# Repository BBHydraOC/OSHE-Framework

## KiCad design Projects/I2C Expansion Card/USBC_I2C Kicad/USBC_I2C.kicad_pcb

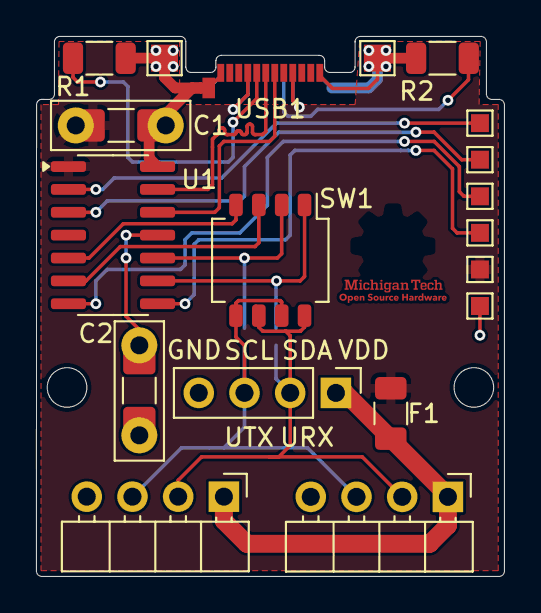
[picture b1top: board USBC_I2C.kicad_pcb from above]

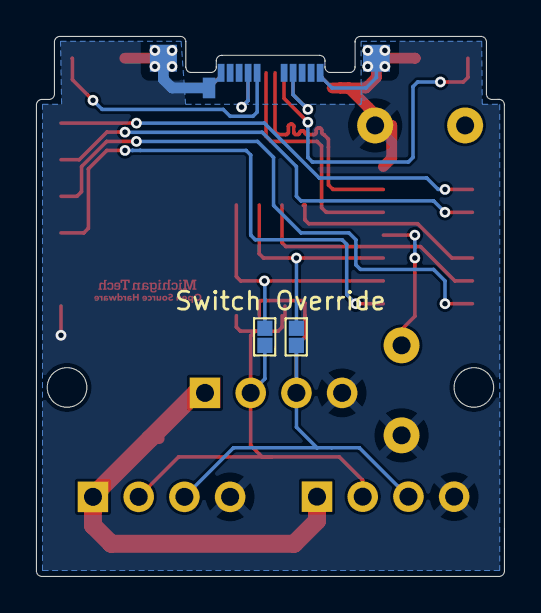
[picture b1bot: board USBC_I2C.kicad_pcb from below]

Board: 2 copper layers, 26.0 x 30.0 mm, 14 parts (2 on the bottom side), 13 nets.

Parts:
2x Pads, 2x Pads#2: Jumper Pads
C1: 0.47uF; C_1206_3216Metric_Pad1.33x1.80mm_HandSolder
C2: 0.22uF; C_1206_3216Metric_Pad1.33x1.80mm_HandSolder
F1: Polyfuse; Fuse_1206_3216Metric
H1, H2: MountingHole; MountingHole_2.2mm_M2
R1: 5.1k; R_1206_3216Metric
R2: Resistors TBD; R_1206_3216Metric
SW1: SW_DIP_x04; SW_DIP_SPSTx04_Slide_Omron_A6H-4101_W6.15mm_P1.27mm
TP3, TP3#2: TestPoint; TestPoint_Pad_1.5x1.5mm
U1: MCP2221AxSL; SOIC-14_3.9x8.7mm_P1.27mm
USB1: USB C Male Connector; USB_C_Plug_Molex_105444

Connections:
GND: C1.1, C2.1, R1.2, R2.2, TP3.1, TP3#2.1, U1.14 (VSS), USB1.A1 (GND), USB1.A12 (GND), USB1.B1 (GND), USB1.B12 (GND), USB1.S1 (SHIELD)
unnamed: U1.13 (D+), USB1.A6 (D+)
unnamed: U1.12 (D-), USB1.A7 (D-)
unnamed: 2x Pads#2.1, SW1.2, U1.10 (SCL)
unnamed: 2x Pads.1, SW1.1, U1.9 (SDA)
unnamed: SW1.4, U1.5 (URx)
unnamed: SW1.3, U1.6 (UTx)
unnamed: C1.2, F1.1, U1.1 (VDD), USB1.A4 (VBUS), USB1.A9 (VBUS), USB1.B4 (VBUS), USB1.B9 (VBUS)
unnamed: C2.2, U1.11 (VUSB)
unnamed: R1.1, USB1.A5 (CC)
unnamed: R2.1, USB1.B5 (VCONN)
Out0: 2x Pads.2, SW1.6, SW1.8
Out1: 2x Pads#2.2, SW1.5, SW1.7

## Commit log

2025-09-03 Added file for ideas had by the OSHE Framework team
2025-09-04 Had a new idea for a module
2025-09-10 Adding files from yesterday
    Proof of concept code for display and Kicad schematic for I2C Adapter
2025-09-10 Worked on KiCad Schematic
2025-09-11 Added new ideas from today's presentation
2025-09-11 Added long messages
    Added support for arbitrarily long data strings [Data]P[Data]P[Data]PE
2025-09-16 Worked on linux script
    Added avaliable memory to the arduino script as well as developed a bash script for reading values from linux.
2025-09-18 Added GPU Temp Support
    Only works with AMD GPUs, but FW Desktop dont have Intel or Nvidia or Multiple GPUs most of the time at present
2025-09-18 Added more sensors to the file
    Still gotta lengthen the message to accomodate all the new data
2025-09-21 Updated USB to I2C
    added values and updated schematic
2025-09-21 Updated to display new data
2025-09-21 Worked on I2C PCB
2025-09-24 Swapped to SMD chip
2025-09-27 Went and added some new ideas
2025-09-28 A couple more ideas
2025-09-30 Built circuit and found some example code
    Found and modified some example code to blink usb status LED and to read I2C and print to console
2025-09-30 Added capacitor values
2025-10-02 Added Female and Male only card variants
2025-10-02 Implemented basic multi-device support
    It weeds out devices that only return 0x07 when queried, and skips outputting those devices. It doesn't add them to the query list.
2025-10-02 Reworked prints to be more readable
2025-10-09 Uploading code not present on github
2025-10-09 Added Vram Utilization and refactored some files
2025-10-09 Added I2C Write example and reformatted display
    I2C write example is literally just the desktop display, and I also refactored the Desktop display's code for ease of porting to different OS or adding new features.
2025-10-15 Added OS Detection in master file
2025-10-15 Implemented OS detection
    Detects if host OS is linux or windows, and then switches to the appropriate functions for the Operating System (WMI doesnt exist on linux lol)
2025-10-17 Added Impedance Matching and added 5V Plane
2025-10-17 Changed display for <10% on cpu and ram
2025-10-20 Fixed trace routing on dual output card
2025-10-21 Reworked pcb to put everything on one board
    Merged the 3 versions into one, added through hole cap holes, added uart switch, fixed the pcb edge
2025-10-22 Added jumpers in case switch doesnt work
2025-10-22 Moved a few traces and fixed edge
2025-10-22 Quicksave
2025-10-22 Fixing some DRC
2025-10-22 Added USB PD Resistors
2025-10-23 Added OCP
2025-10-24 Reworked the PCB to better route traces
2025-10-24 Swapped switches
2025-10-27 Rerouted a few traces
2025-10-27 Added silkscreen for switch pinouts
